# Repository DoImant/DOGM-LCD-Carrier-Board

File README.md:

# Carrier board for displays of the DOGMxxxxA series.

These DOGM text displays are available in variants with 1x8 (EA DOGM081x-A), 2x16 (EA DOGM162x-A) 
and 3x16 characters (EA DOGM163x-A). The carrier board is suitable for all three variants.

This board should support all backlights (white, yellow/green, blue, red, amber, rgb full color),
but only amber was tested. The display must be connected with 3.3V.
The data transmission to the display takes place via the SPI protocol.

## DOGM LCD Datasheet

[Datasheet](https://github.com/DoImant/Stuff/blob/main/DOGM-LCD-Carrier-Board/Datasheet/dogm-lcd-eng.pdf)

## Pictures
DOGM LCD with Backlightmodule

Carrier board front

Carrier board back

Carrier board with DOGM LCD

Display with switched off backlight.

Display with low regulated backlight.

Display with highly regulated backlight.

## Arduino Library for DOGMxxxxA Devices

[Library] (https://github.com/DoImant/Stuff/tree/main/DOGM-LCD-Carrier-Board/Arduino-Library/DOGM_7036)

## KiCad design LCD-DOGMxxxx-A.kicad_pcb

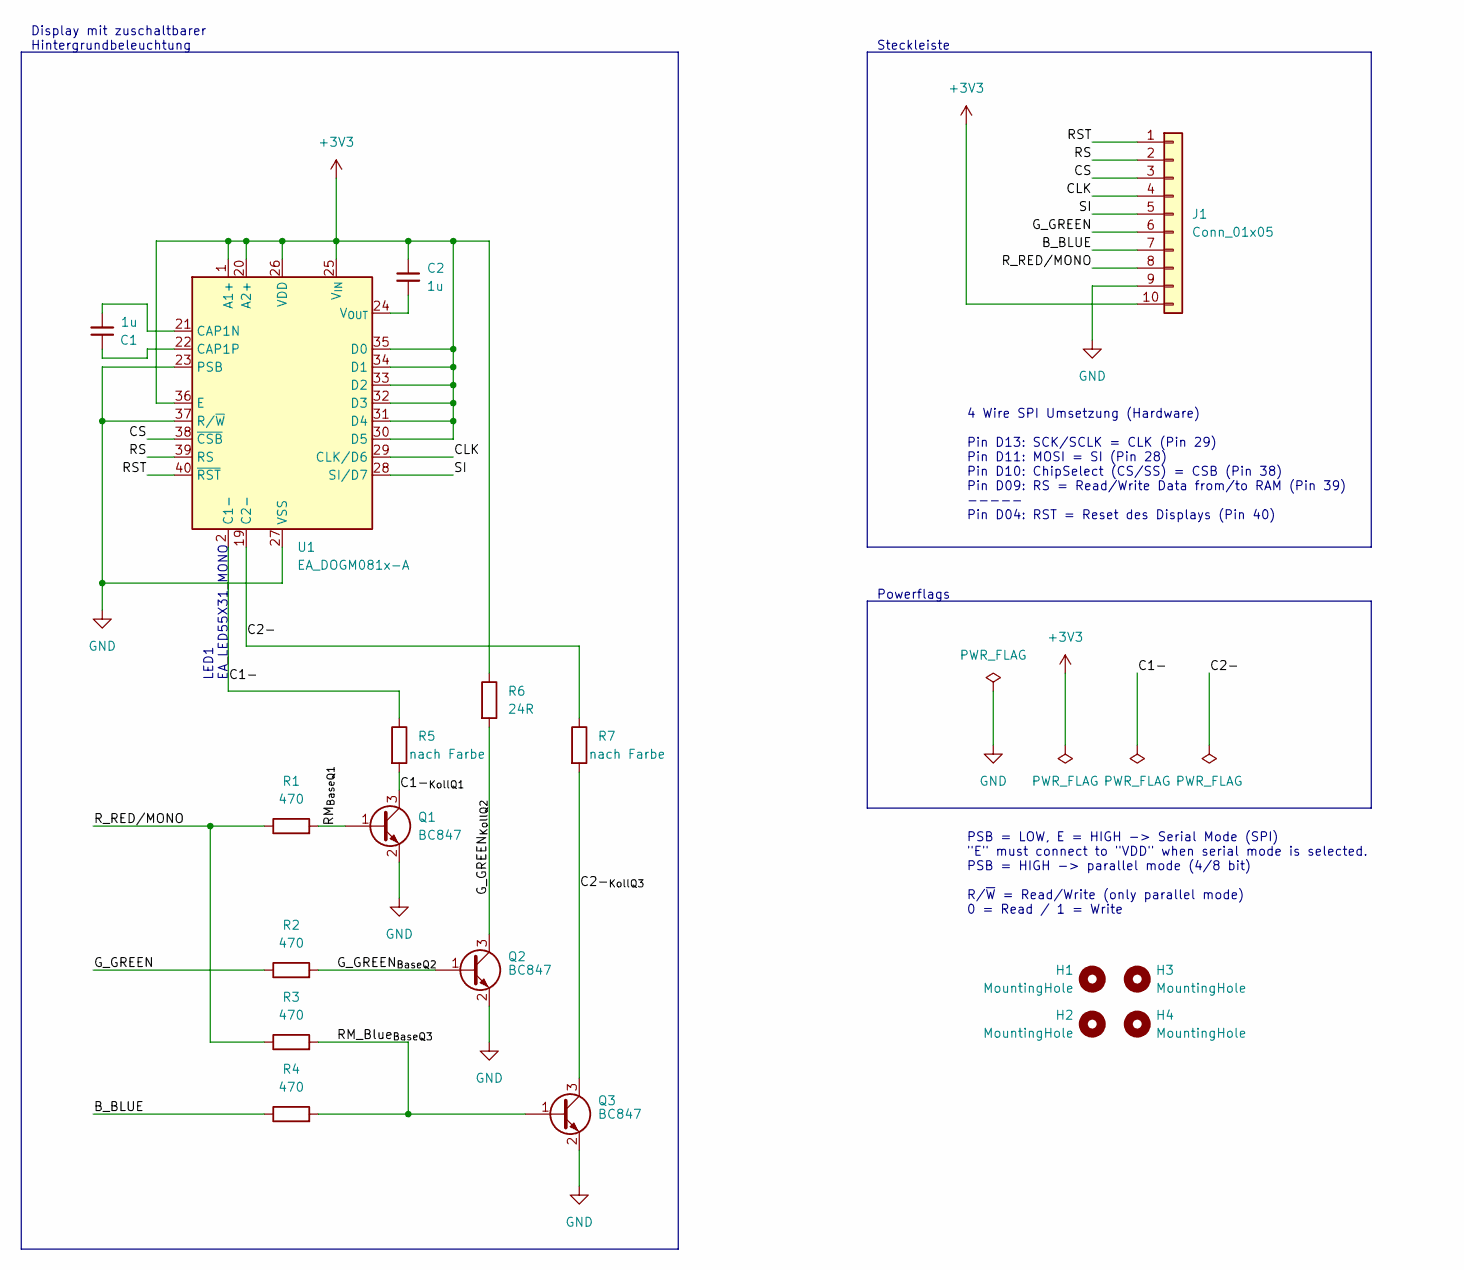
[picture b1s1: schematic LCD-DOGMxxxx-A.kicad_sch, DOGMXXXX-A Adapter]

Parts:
C1, C2: 1u; C_1206_3216Metric_Pad1.33x1.80mm_HandSolder
H1, H2, H3, H4: MountingHole; MountingHole_3.2mm_M3
J1: Conn_01x05; PinHeader_1x10_P2.54mm_Vertical
Q1, Q2, Q3: BC847; SOT-23
R1, R2, R3, R4: 470; R_1206_3216Metric_Pad1.30x1.75mm_HandSolder
R5, R7: nach Farbe; R_1206_3216Metric_Pad1.30x1.75mm_HandSolder
R6: 24R; R_1206_3216Metric_Pad1.30x1.75mm_HandSolder
U1: EA_DOGM081x-A; EA_DOGMxxxx-A_55x27mm_P2.54

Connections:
+3V3: C2.1, J1.10, R6.1, U1.1 (A1+), U1.20 (A2+), U1.25 (V_{IN}), U1.26 (VDD), U1.30 (D5), U1.31 (D4), U1.32 (D3), U1.33 (D2), U1.34 (D1), U1.35 (D0), U1.36 (E)
/B_BLUE: J1.7, R4.1
/C1-: R5.1, U1.2 (C1-)
/C1-_{KollQ1}: Q1.3 (C), R5.2
/C2-: R7.1, U1.19 (C2-)
/C2-_{KollQ3}: Q3.3 (C), R7.2
/CLK: J1.4, U1.29 (CLK/D6)
/CS: J1.3, U1.38 (~CSB)
/G_GREEN: J1.6, R2.1
/G_GREEN_{BaseQ2}: Q2.1 (B), R2.2
/G_GREEN_{KollQ2}: Q2.3 (C), R6.2
/RM_Blue_{BaseQ3}: Q3.1 (B), R3.2, R4.2
/RM_{BaseQ1}: Q1.1 (B), R1.2
/RS: J1.2, U1.39 (RS)
/RST: J1.1, U1.40 (~RST)
/R_RED/MONO: J1.8, R1.1, R3.1
/SI: J1.5, U1.28 (SI/D7)
GND: J1.9, Q1.2 (E), Q2.2 (E), Q3.2 (E), U1.23 (PSB), U1.27 (VSS), U1.37 (R/~W)
unnamed: C1.1, U1.22 (CAP1P)
unnamed: C1.2, U1.21 (CAP1N)
unnamed: C2.2, U1.24 (V_{OUT})

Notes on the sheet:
PSB = LOW, E = HIGH -> Serial Mode (SPI) "E" must connect to "VDD" when serial mode is selected. PSB = HIGH -> parallel mode (4/8 bit) R/~{W} = Read/Write (only parallel mode) 0 = Read / 1 = Write
Steckleiste
Display mit zuschaltbarer Hintergrundbeleuchtung
LED1 EA_LED55X31_MONO
4 Wire SPI Umsetzung (Hardware) Pin D13: SCK/SCLK = CLK (Pin 29) Pin D11: MOSI = SI (Pin 28) Pin D10: ChipSelect (CS/SS) = CSB (Pin 38) Pin D09: RS = Read/Write Data from/to RAM (Pin 39) ----- Pin D04: RST = Reset des Displays (Pin 40)
Powerflags

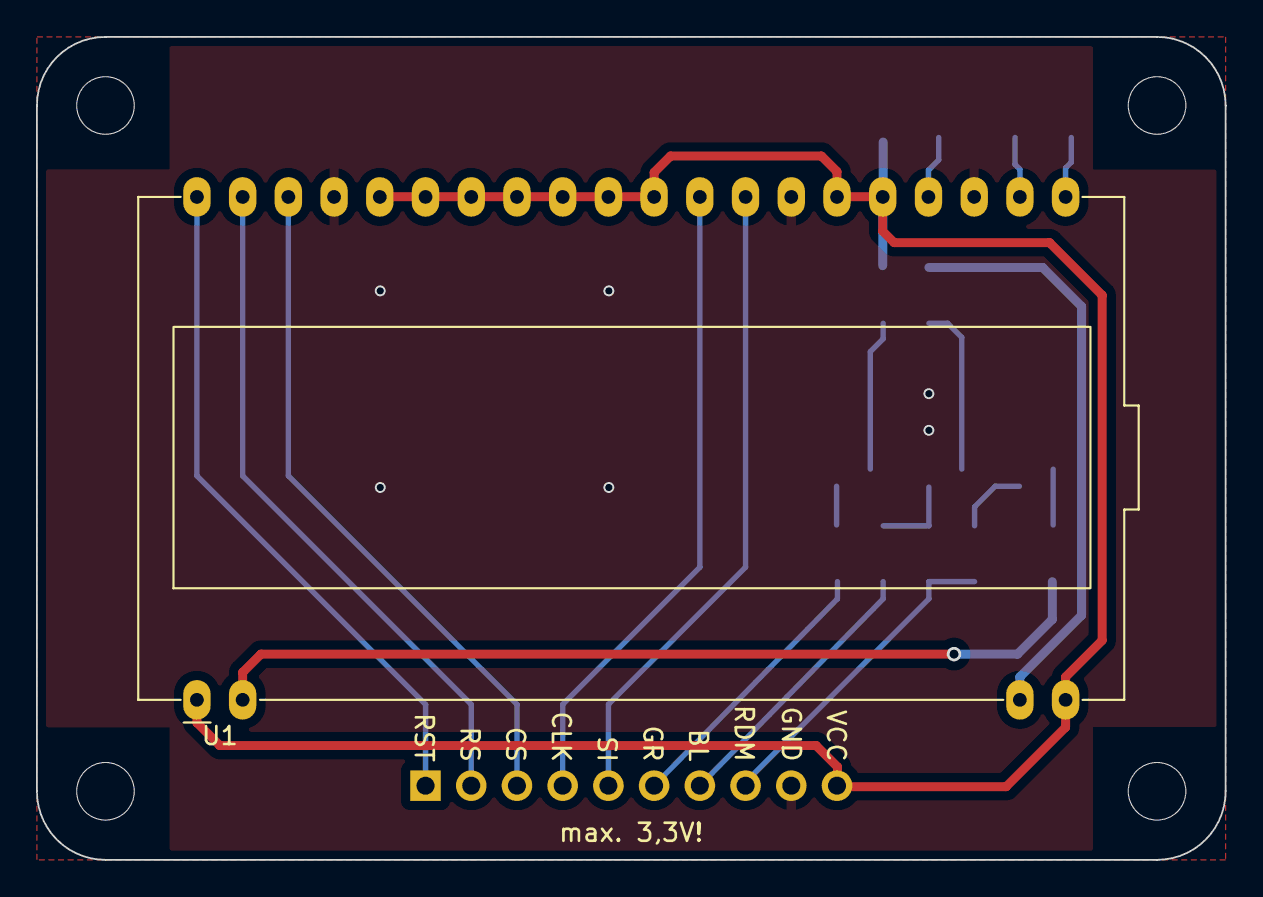
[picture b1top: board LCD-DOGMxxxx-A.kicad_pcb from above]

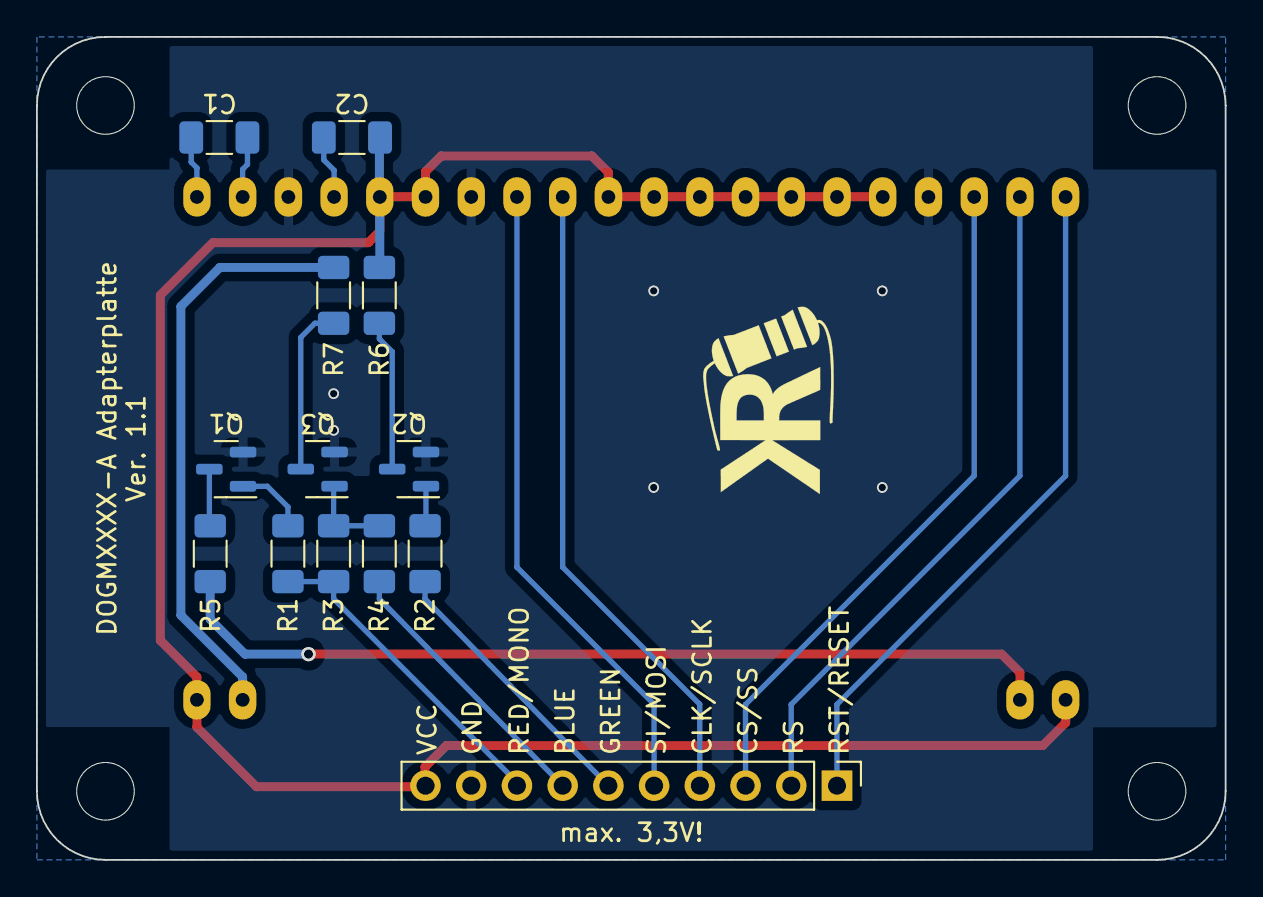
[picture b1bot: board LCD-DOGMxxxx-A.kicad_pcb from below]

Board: 2 copper layers, 66.0 x 45.7 mm, 18 parts (13 on the bottom side), 21 nets.
